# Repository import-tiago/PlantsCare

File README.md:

# PlantsCare

PlantsCare is an IoT device for ultra low power standalone capacitive soil moisture meter.

## Features
##### Controller Device / [16-bit, RISC, MSP430 FRAM-based Microcontroller](https://github.com/import-tiago/PlantsCare/blob/master/Hardware/3.%20Datasheets/MCU/MSP430%20-%20Datasheet.pdf)

##### Wireless Technology / [Bluetooth Low Energy - CSR1010](https://github.com/import-tiago/WorkshySwitch/blob/master/Hardware/3.%20Datasheets/BLE/CSR1010%20(BLE%20IC)%20-%20Datasheet.pdf)

##### Low Power Requirements / [CR2450 Battery Life > 2 years](https://github.com/import-tiago/PlantsCare/blob/master/Hardware/3.%20Datasheets/Battery/CR2450.pdf)

##### Hardware Project / [Autodesk EAGLE](https://www.autodesk.com/products/eagle/free-download)

##### Firmware Project / [Code Composer Studio (CCS)](http://www.ti.com/tool/CCSTUDIO)

## PCB Gerber Preview

## Schematic

## Bill of Materials
| Qty | Parts | Description | Value | Package |
|--|--|--|--|--|
1|R2|SMD Resistor|47k ±5%|R0603
1|R4|SMD Resistor|1M ±5%|R0603
2|R6/R7|SMD Resistor|0R ±5%|R0603
3|R1/R3/R5|SMD Resistor|10k ±5%|R0603
1|C4|SMD Capacitor|1 nF / 50V|C0603
1|C7|SMD Capacitor|1 uF / 6.3V|C0603
1|C1|SMD Capacitor|10 uF / 50V|C0603
2|C2/C3|SMD Capacitor|100 nF / 50V|C0603
2|C5/C6|SMD Capacitor|22 pF / 50V|C0603
1|D1|Small Signal Fast Switching Diode|1N4148|SOD523
1|LED1|SMD LED|Blue|L0805
1|U1|Microcontroller|MSP430FR4133IG48R|TSSOP-48
1|Q1|SMD Crystal|32.768 kHz|3.2 x 1.5
1|PCB1|Qualcomm BLE CSRmesh Module|BLE-1010 MPCBA|-
1|BT1|Through Hole Coin Cell Battery Holder|CR2450|-
1|S1|SMD Switch/Momentary/Normally Open|SPST-NO|3 x 6 mm
1|CN1|Through Hole Connector/4 Pins/2 mm pitch|-|-

### Contributing
0. Give this project a :star:
1. Create an issue and describe your idea.
2. [Fork it](https://github.com/import-tiago/PlantsCare/fork).
3. Create your feature branch (`git checkout -b my-new-feature`).
4. Commit your changes (`git commit -a -m "Added feature title"`).
5. Publish the branch (`git push origin my-new-feature`).
6. Create a new pull request.
7. Done! :heavy_check_mark:

### License Information
<br /><span xmlns:dct="http://purl.org/dc/terms/" property="dct:title">PlantsCare</span> by <a xmlns:cc="http://creativecommons.org/ns#" href="https://github.com/import-tiago" property="cc:attributionName" rel="cc:attributionURL">Tiago Silva</a> is licensed under a <a rel="license" href="http://creativecommons.org/licenses/by-sa/4.0/">Creative Commons Attribution-ShareAlike 4.0 International License</a>.<br />Permissions beyond the scope of this license may be available at <a xmlns:cc="http://creativecommons.org/ns#" href="https://twitter.com/import_tiago" rel="cc:morePermissions">tiagodepaulasilva@gmail.com</a>.

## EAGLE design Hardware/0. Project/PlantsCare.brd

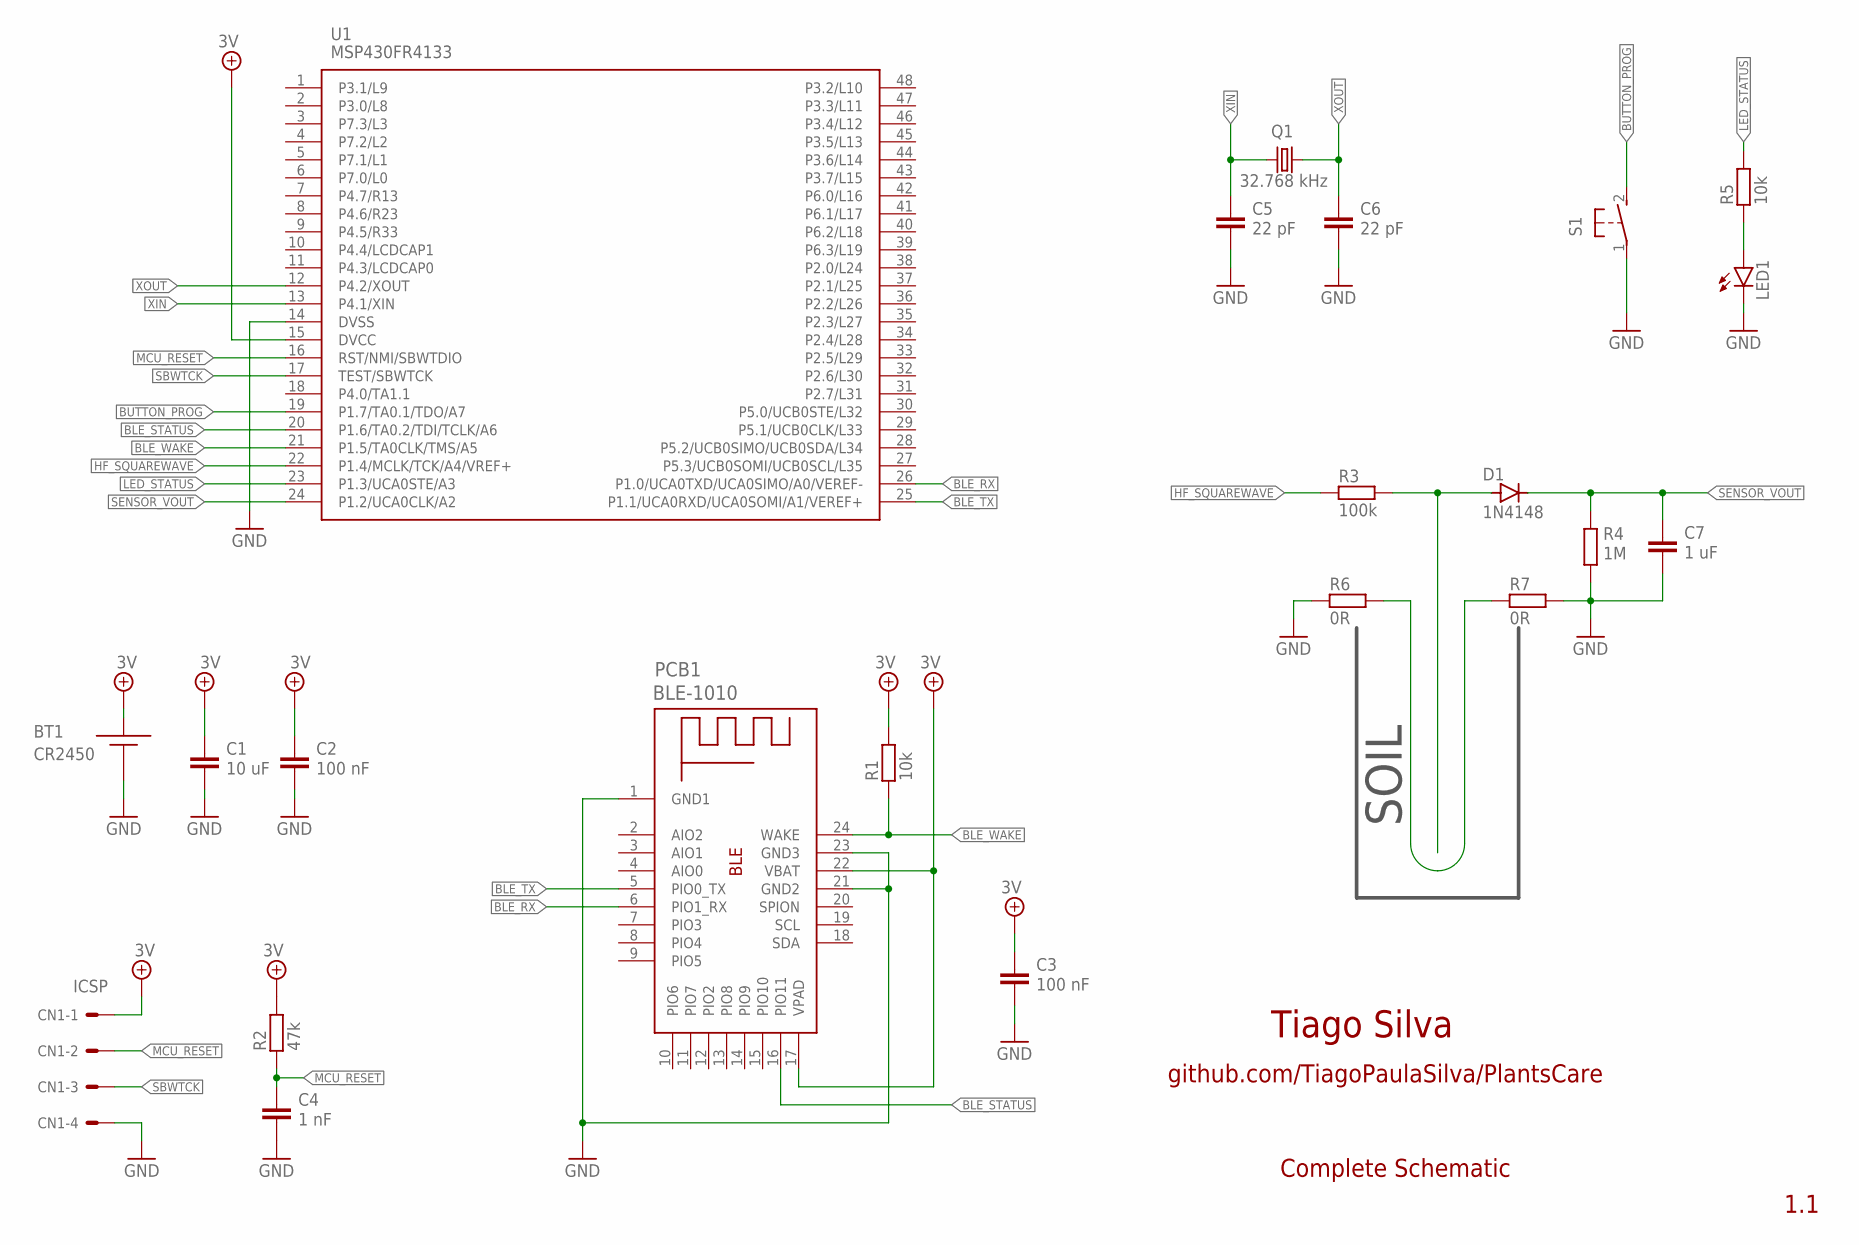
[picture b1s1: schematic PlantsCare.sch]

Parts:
BT1: CR2450; 1053
C1: 10 uF; C0603
C2, C3: 100 nF; C0603
C4: 1 nF; C0603
C5, C6: 22 pF; C0603
C7: 1 uF; C0603
CN1: ICSP; 7395-04
D1: 1N4148; SOD523
LED1: LEDCHIP-LED0805; CHIP-LED0805
PCB1: BLE-1010
Q1: 32.768 kHz; 3.2X1.5
R1, R5: 10k; R0603
R2: 47k; R0603
R3: 100k; R0603
R4: 1M; R0603
R6, R7: 0R; R0603
S1: DTSM-3
U1: MSP430FR4133; SOP50P810X120-48N

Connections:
3V: BT1.2 (3V), C1.1, C2.1, C3.1, CN1.1, PCB1.17 (VPAD), PCB1.22 (VBAT), R1.1, R2.1, U1.15 (DVCC)
BLE_RX: PCB1.6 (PIO1_RX), U1.26 (P1.0/UCA0TXD/UCA0SIMO/A0/VEREF-)
BLE_STATUS: PCB1.16 (PIO11), U1.20 (P1.6/TA0.2/TDI/TCLK/A6)
BLE_TX: PCB1.5 (PIO0_TX), U1.25 (P1.1/UCA0RXD/UCA0SOMI/A1/VEREF+)
BLE_WAKE: PCB1.24 (WAKE), R1.2, U1.21 (P1.5/TA0CLK/TMS/A5)
BUTTON_PROG: S1.2, U1.19 (P1.7/TA0.1/TDO/A7)
ELECTRODE_CAP1: R6.1, R7.2
ELECTRODE_CAP2: D1.A, R3.1
GND: BT1.1 (GND), C1.2, C2.2, C3.2, C4.2, C5.2, C6.2, C7.2, CN1.4, LED1.C, PCB1.1 (GND1), PCB1.21 (GND2), PCB1.23 (GND3), R4.2, R6.2, R7.1, S1.1, U1.14 (DVSS)
HF_SQUAREWAVE: R3.2, U1.22 (P1.4/MCLK/TCK/A4/VREF+)
LED_STATUS: R5.1, U1.23 (P1.3/UCA0STE/A3)
MCU_RESET: C4.1, CN1.2, R2.2, U1.16 (RST/NMI/SBWTDIO)
unnamed: LED1.A, R5.2
SBWTCK: CN1.3, U1.17 (TEST/SBWTCK)
SENSOR_VOUT: C7.1, D1.C, R4.1, U1.24 (P1.2/UCA0CLK/A2)
XIN: C5.1, Q1.1, U1.13 (P4.1/XIN)
XOUT: C6.1, Q1.2, U1.12 (P4.2/XOUT)

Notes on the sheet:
Tiago Silva
github.com/TiagoPaulaSilva/PlantsCare
SOIL
1.1
Complete Schematic

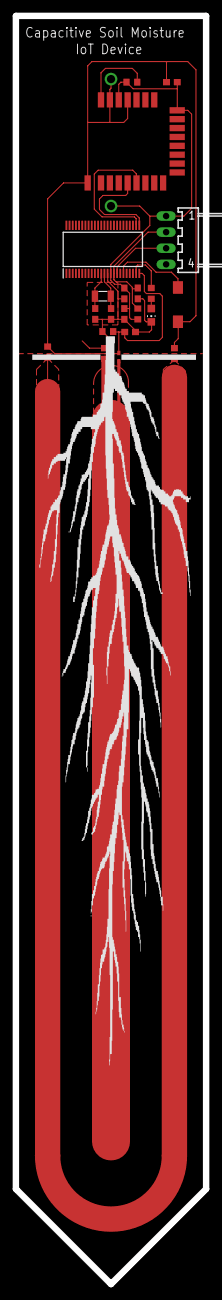
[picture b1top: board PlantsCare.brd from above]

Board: 2 copper layers, 30.0 x 200.0 mm, 22 parts (0 on the bottom side), 17 nets.

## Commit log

2019-07-06 Schematic frame info updated
2019-07-06 PCB layout developed
2019-07-06 Hardware folder created
2019-07-06 Battery Silk Screen Removed
2019-07-06 Added gerber PCB image preview
2019-07-06 PCB image preview resized
2019-07-07 Changed folder structure
2019-07-07 Duplicate file removed (eagle.epf)
2019-07-07 Firmware project created
2019-07-07 Changed firmware folder structure
2019-07-07 Project name changed to 'PlantsCare'
2019-07-07 BOM .csv file formatted as GitHub needed
2019-07-07 BOM .csv file updated
2019-07-07 PlantsCare flowchart added
2019-07-08 Flowchart updated
2019-07-09 Readme updated
2019-07-10 CR2450 Battery added
2019-07-20 Schematic organization improved
2019-07-20 Schematic image generated
2019-07-22 .gitattributes added
2019-07-22 .gitattributes file added
2019-08-10 Firmware started
2019-08-10 LED Blinky Working
2019-08-12 1MHz signal generated
2019-08-12 P8 registers removed
2019-08-14 ADC reading high freq. waveform working
2019-08-14 Schematic updated to 1.2 revision
    --------------------------------------------------------------------
    * HF_SQUAREWAVE signal removed from P7.0 and connected to P1.4
    - P1.4 has a native function thats provides a MCLK clock as OUTPUT. This way, isn't necessery manually generates a high freq. signal with another pin.
    --------------------------------------------------------------------
    * BLE_WAKE signal added to P1.5
    - This will allows the MCU wake-up the BLE with a single low level pulse.
2019-08-14 PCB layout needs to be updated to 1.2
2019-08-14 Setup_BLE() implemented
2019-08-14 Get_Soil_Moisture() implemented
2019-08-14 setup_BLE() new AT command added
2019-08-14 Read_PROG_Button() implemented
2019-08-15 FRAM_Read() and FRAM_Write() implemented
2019-08-15 FRAM Read/Write allow negative numbers
2019-08-16 R3 value changed to fix SENSOR_VOUT waveform
2019-08-16 Calibration process bugs fixed
2019-08-16 FRAM Read/Write functions with void return
2019-08-28 Minor improvemets
2019-08-28 .gitattributes removed
2019-11-16 Images added
2019-11-16 Gerber image updated
2023-07-21 usernames in URLs updated

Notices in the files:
parts and their libraries:
crystal-geyer_V1_0: Copyright: Geyer-Electronic
